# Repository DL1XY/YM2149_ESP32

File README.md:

# Yamaha YM2149 ESP32 Soundmodule

## _ATTENTION_
**_DON'T FLASH THE ESP32 WHILE CONNECTED TO POWERSUPPLY ! THIS COULD DESTROY THE ESP32 ! JUST USE AN USB CABLE !_**

## Abstract
This soundmodule enables YM2149 soundgeneration via a web interface in a dedicated WiFi Network or your existing WLAN. 

The YM2149 is Yamaha's pin- and register compatible version of [General Instrument's AY-3-8910](https://en.wikipedia.org/wiki/General_Instrument_AY-3-8910) which was used in legendary video game consoles and home computers like
- Intellivision
- Vectrex
- Amstrad CPC
- MSX
- later ZX Spectrum

The soundchip is controlled by an [Espressif ESP32](ttps://www.espressif.com/en/products/socs/esp32/overview) which also works as
- Webserver providing HTML/JavaScript documents to control the soundchip via browser
- Application Server providing a REST interface
- clock generator for YM2149
- (WiFi Access Point)

## HW Revision 1.0

### Schematic
 <!-- .element height="10%" width="10%" -->

### Features
- HW-104 (PAM8403) Amplifier Board
- Breadboard Powersupply(3V3 and 5V) Board 
- ESP32-WROOM Devkit Board
- ALPS RV16 A10K logarithmic potentiometer used
- 6.3mm Audiojack

### Bugs
[ ] Mounting holes at random positions

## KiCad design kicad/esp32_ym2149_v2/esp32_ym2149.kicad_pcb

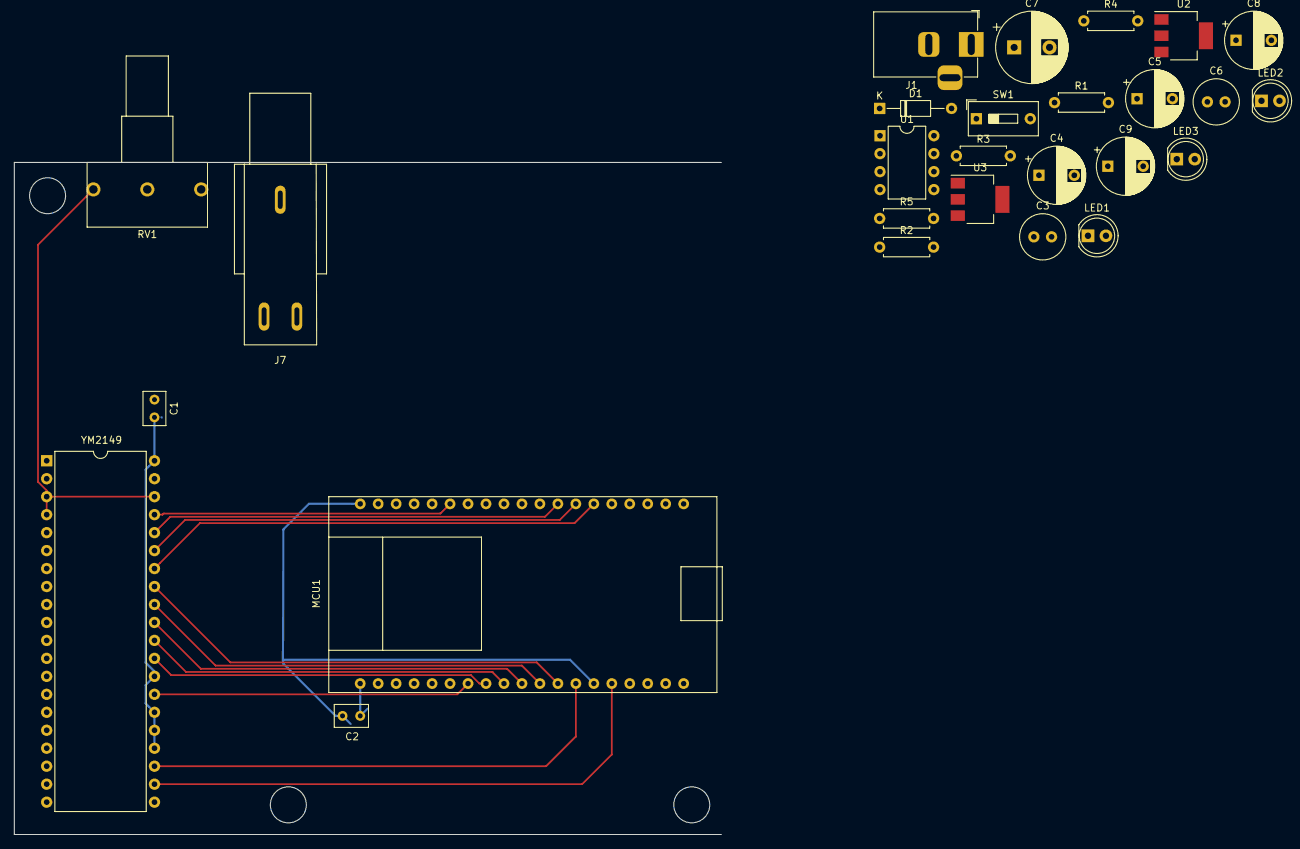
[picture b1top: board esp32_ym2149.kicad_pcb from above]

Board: 2 copper layers, 99.9 x 95.0 mm, 27 parts (0 on the bottom side), 29 nets.

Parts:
C1, C2: 10nF; C_Rect_L4.6mm_W3.0mm_P2.50mm_MKS02_FKP02
C3, C6: 0.1uF; C_Radial_D6.3mm_H5.0mm_P2.50mm
C4, C5: 10uF; CP_Radial_D8.0mm_P5.00mm
C7: 100uF; CP_Radial_D10.0mm_P5.00mm
C8, C9: 22uF; CP_Radial_D8.0mm_P5.00mm
D1: 1N5400; D_DO-35_SOD27_P10.16mm_Horizontal
J1: 9V DC; BarrelJack_Horizontal
J7: AudioJack3; AudioJack 6.5mm
LED1: POWER_LED; LED_D5.0mm
LED2: 3V3_LED; LED_D5.0mm
LED3: 5V_LED; LED_D5.0mm
MCU1: ESP32-DEVKITC-32D; ESP32-WROOM-Devkit
R1, R2: 1.2K; R_Axial_DIN0207_L6.3mm_D2.5mm_P7.62mm_Horizontal
R3: 1k; R_Axial_DIN0207_L6.3mm_D2.5mm_P7.62mm_Horizontal
R4: 520; R_Axial_DIN0207_L6.3mm_D2.5mm_P7.62mm_Horizontal
R5: 220; R_Axial_DIN0207_L6.3mm_D2.5mm_P7.62mm_Horizontal
RV1: 10 kOhm; ALPHA POT 16 RV16
SW1: SW_SPST; SW_DIP_SPSTx01_Slide_9.78x4.72mm_W7.62mm_P2.54mm
U1: LM386; DIP-8_W7.62mm
U2: AMS1117-5.0; SOT-223-3_TabPin2
U3: AMS1117-3.3; SOT-223-3_TabPin2
YM2149: Yamaha_YM2149; DIP-40_W15.24mm

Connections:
+3.3V: C2.2, C9.1, MCU1.1, R5.1, U3.2
+5V: C1.2, C3.2, C8.1, R4.1, U1.6, U2.2, YM2149.24, YM2149.25, YM2149.26, YM2149.28, YM2149.40
/RAWAUDIO: RV1.3, YM2149.3, YM2149.4, YM2149.38
BC1: MCU1.8, YM2149.29
BDIR: MCU1.7, YM2149.27
CLOCK: MCU1.15, YM2149.22
DA0: MCU1.25, YM2149.37
DA1: MCU1.31, YM2149.36
DA2: MCU1.32, YM2149.35
DA3: MCU1.33, YM2149.34
DA4: MCU1.12, YM2149.33
DA5: MCU1.11, YM2149.32
DA6: MCU1.10, YM2149.31
DA7: MCU1.9, YM2149.30
GNDREF: C1.1, C2.1, C3.1, C4.2, C6.2, C7.2, C8.2, C9.2, J1.2, J7.S, LED1.1, LED2.1, LED3.1, MCU1.14, MCU1.20, RV1.1, U1.2, U1.4, U2.1, U3.1, YM2149.1
unnamed: C4.1, U1.7
unnamed: C5.1, R1.2
unnamed: C5.2, U1.8
unnamed: C6.1, R2.2
unnamed: C7.1, D1.1, U2.3, U3.3
unnamed: D1.2, R3.1, SW1.2
unnamed: J1.1, SW1.1
unnamed: J7.R, J7.T, R2.1, U1.5
unnamed: LED1.2, R3.2
unnamed: LED2.2, R5.2
unnamed: LED3.2, R4.2
unnamed: R1.1, U1.1
RESET: MCU1.13, YM2149.23
RV_AUDIO: RV1.2, U1.3

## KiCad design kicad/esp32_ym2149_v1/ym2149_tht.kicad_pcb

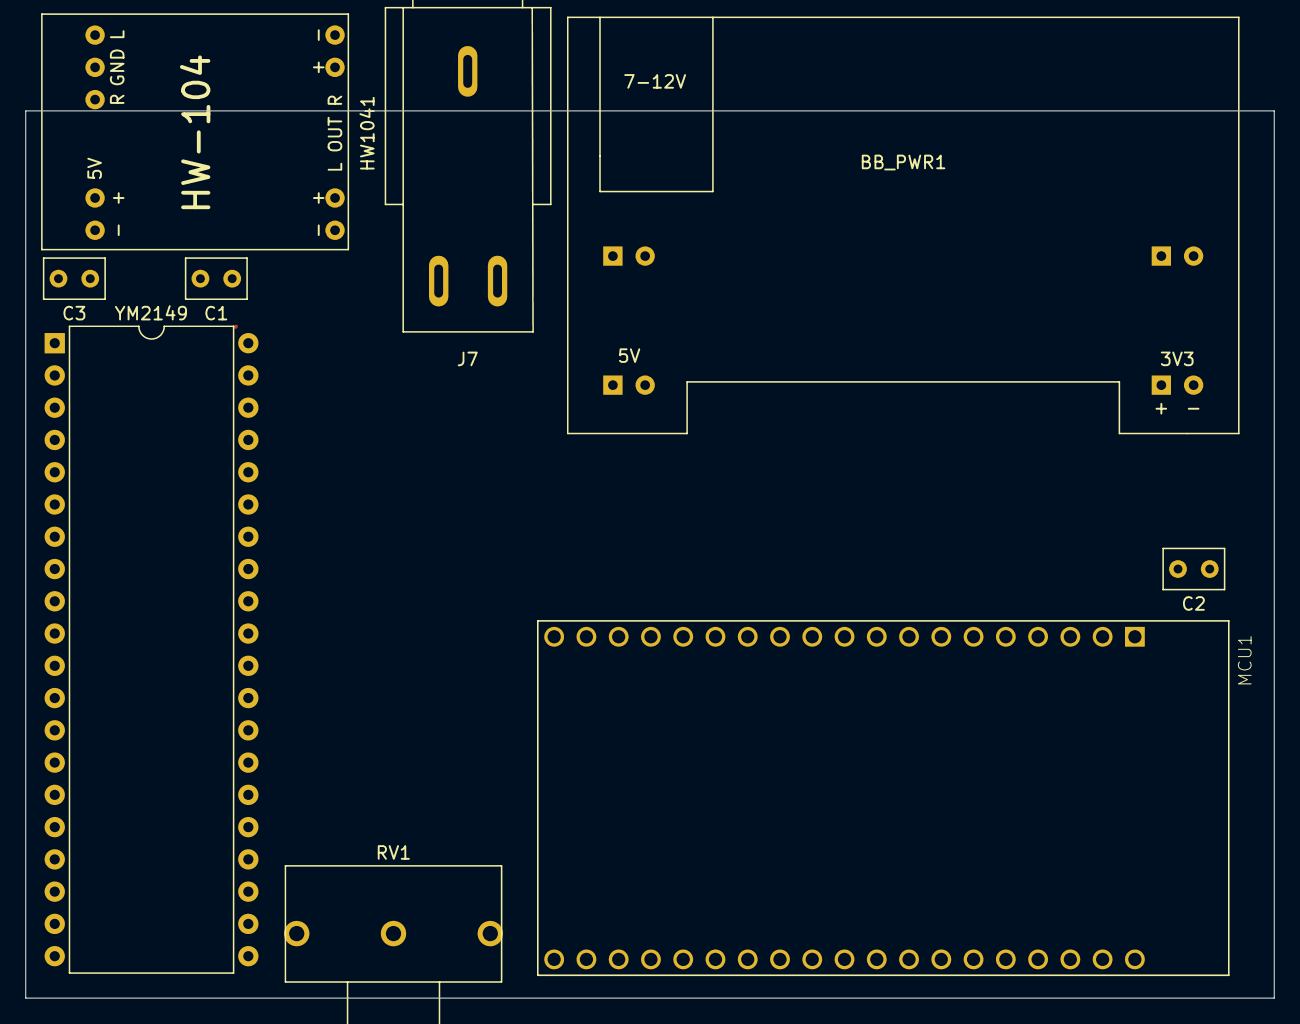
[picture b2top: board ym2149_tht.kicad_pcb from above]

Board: 2 copper layers, 98.3 x 69.8 mm, 9 parts (0 on the bottom side), 20 nets.

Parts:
BB_PWR1: BreadboardPowerSupply; Breadboard_Powersupply_3V3_5V
C1, C2, C3: 10nF; C_Rect_L4.6mm_W3.0mm_P2.50mm_MKS02_FKP02
HW1041: HW-104_Board; HW-104 Board
J7: AudioJack3; AudioJack 6.5mm
MCU1: ESP32-DEVKITC-32D; MODULE_ESP32-DEVKITC-32D
RV1: 10 kOhm; ALPHA POT 16 RV16
YM2149: Yamaha_YM2149; DIP-40_W15.24mm

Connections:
+3.3V: BB_PWR1.3, C2.2, MCU1.1
+5V: BB_PWR1.1, C1.2, C3.2, HW1041.4, YM2149.24, YM2149.25, YM2149.26, YM2149.28, YM2149.40
BC1: MCU1.15, YM2149.29
BDIR: MCU1.13, YM2149.27
CLOCK: MCU1.36, YM2149.22
DA0: MCU1.33, YM2149.37
DA1: MCU1.32, YM2149.36
DA2: MCU1.31, YM2149.35
DA3: MCU1.25, YM2149.34
DA4: MCU1.12, YM2149.33
DA5: MCU1.11, YM2149.32
DA6: MCU1.10, YM2149.31
DA7: MCU1.9, YM2149.30
GNDREF: BB_PWR1.2, BB_PWR1.4, C1.1, C2.1, C3.1, HW1041.2, HW1041.5, MCU1.14, MCU1.20, RV1.1, YM2149.1
unnamed: HW1041.1, HW1041.3, RV1.2
unnamed: HW1041.6, HW1041.9, J7.S
unnamed: HW1041.7, J7.T
unnamed: HW1041.8, J7.R
unnamed: RV1.3, YM2149.3, YM2149.4, YM2149.38
RESET: MCU1.35, YM2149.23

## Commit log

2020-03-17 init commit
2020-03-17 cleanup
2020-03-18 new vue added
2020-03-20 new web content added
2020-03-20 more fetch() added
2020-03-21 rest handler update
2020-03-21 Fritzing added !
2020-03-22 task handling modified, more debug
2020-03-26 small fixes, more logs added
2020-03-26 cmd queue fix
2020-03-27 sizeof struct bugfix, cleanup
2020-03-27 timer isr fixed
2020-03-27 Formatting
2020-03-28 js fix, cleanup, debug msgs added
2020-03-28 svg for envelope ahepes added
2020-03-28 KiCAD files added
2020-03-28 SVG Env Shape interaction added
2020-03-28 SVG look modified, img based svg added
2020-03-29 kicad schema modified
2020-03-29 power supply and audio amp added
2020-03-30 netlist 1st draft added
2020-03-31 pcb draft extended
2020-03-31 some minor changes, cleanup
2020-04-05 some layout changes
2020-04-13 minor changes, sdk update
2020-04-20 new symbols and footprints added
2020-04-21 layout changes
2020-04-23 README modified, Gerber files added, PCB modified
2020-04-24 GPIOs changed
2020-04-28 folder renamed, v2 folder created
2020-04-28 secrets_example.h added
2020-04-28 docs added
2020-04-28 README modified, schematic PNG added
2020-04-28 v2 started, docs added, cleanup
2020-05-01 pcb modified, wifi jumper added
2023-05-14 Rename package.lock to package-lock.json
